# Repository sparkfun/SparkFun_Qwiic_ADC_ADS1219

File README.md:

[*SparkFun Qwiic 24 Bit ADC - 4 Channel (ADS1219) (SEN-27544)*](https://www.sparkfun.com/sparkfun-qwiic-24-bit-adc-4-channel-ads1219.html)

A lot of the time you just need to add more analog inputs to solve a problem. It happens. The SparkFun Qwiic 24-Bit ADC can provide four channels of I2C controlled ADC input to your Qwiic enabled project. These channels can be used as single-ended inputs, or in pairs for differential inputs, running at sample rates of up to 1kHz. What makes this ADC even more powerful is that it has a programmable x1 or x4 gain amplifier that lets you "zoom in" on a very small change in analog voltage (but will still effect your input range and resolution). Utilizing our handy Qwiic system, it is easy to connect it to the rest of your system. However, we have broken out 0.1"-spaced pads too in case you prefer to use a breadboard. The analog inputs and reference pins are all broken out on 0.1"-spaced pads too. This board does not have screw terminals - there was not enough room!

The ADS1219 can use its own internal 2.048V voltage reference for measurements, or you can provide your own reference via the REFP and REFN breakout pads. You can also provide your own VDDA (AVDD) by opening the jumper and connecting a voltage to the VDDA pad. This ADC board has eight address jumpers that let you choose one of sixteen unique addresses (0x40 to 0x4F). With these, you can connect up to sixteen of these on the same I2C bus and have 64 channels of ADC. The maximum resolution of the converter is 24-bits, corresponding to 244.14nV per count at a gain of x1. At a gain of x4, the resolution is 61.04nV per count. Note: the effective resolution is limited to 20-bits.

Repository Contents
-------------------

* **/docs** - GitHub pages documentation files
* **/Documentation** - TI datasheet 
* **/Hardware** - KiCad design files (_pcb, _sch), Schematic (PDF)
* **/Production** - Production panel files (_pcb, gerbers)

Documentation
--------------
* [**Arduino Library**](https://github.com/sparkfun/SparkFun_ADS1219_Arduino_Library) - Arduino library for the ADS1219.
* [**Hookup Guide**](https://docs.sparkfun.com/SparkFun_Qwiic_ADC_ADS1219/)

Product Versions
-----------------

* [SPX-23455](https://www.sparkfun.com/sparkx-qwiic-24-bit-adc-4-channel-ads1219.html) - Original SparkX release.
* [SEN-27544](https://www.sparkfun.com/sparkfun-qwiic-24-bit-adc-4-channel-ads1219.html) - Initial SparkFun release.

License Information
-------------------

This product is _**open source**_! 

Please review the LICENSE.md file for license information. 

If you have any questions or concerns on licensing, please contact technical support on our [SparkFun forums](https://forum.sparkfun.com/viewforum.php?f=152).

Distributed as-is; no warranty is given.

- Your friends at SparkFun.

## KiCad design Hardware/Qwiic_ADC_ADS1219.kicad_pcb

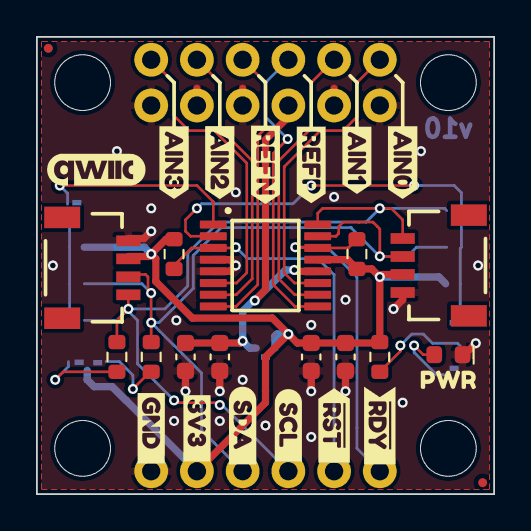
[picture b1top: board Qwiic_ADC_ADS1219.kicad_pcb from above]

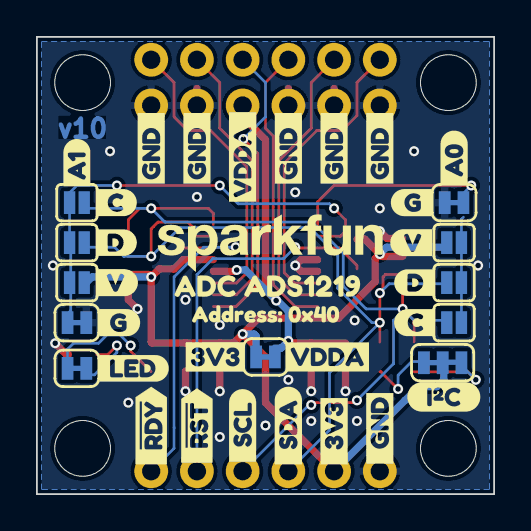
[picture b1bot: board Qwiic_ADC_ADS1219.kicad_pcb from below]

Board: 4 copper layers, 25.4 x 25.4 mm, 75 parts (39 on the bottom side), 19 nets.

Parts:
C1, C3: 2.2uF; C_0603_1608Metric
C2, C4: 0.1uF; C_0603_1608Metric
D1: Red; LED_0603_1608Metric_Red
FID1, FID3: Fiducial_0.5mm; Fiducial_0.5mm_Mask1mm
J1, J2: Qwiic_RA; JST_SMD_1.0mm-4_Black
J3, J4: Conn_01x06; 1x06
J5: Conn_01x02; 1x02
J6: I2C; 1x04
JP1, JP2: Jumper_2_NC_Trace
JP3: Jumper_3_NC-2_Trace
JP4, JP8: G; Jumper_2_NC_Trace
JP5, JP9: V; Jumper_2_NO
JP6, JP10: D; Jumper_2_NO
JP7, JP11: C; Jumper_2_NO
R1: 1k; R_0603_1608Metric
R2, R3: 2.2k; R_0603_1608Metric
R4, R5: 10k; R_0603_1608Metric
ST1, ST2, ST3, ST4: Standoff
U1: ADS1219IPW; TSSOP-16
kibuzzard-64C3B30F: G***; kibuzzard-64C3B30F
kibuzzard-64C3BD7A: G***; kibuzzard-64C3BD7A
kibuzzard-64C36D1A: G***; kibuzzard-64C36D1A
kibuzzard-64C36D2D: G***; kibuzzard-64C36D2D
kibuzzard-64C36D5B: G***; kibuzzard-64C36D5B
kibuzzard-64C36D6C: G***; kibuzzard-64C36D6C
kibuzzard-64C36D47: G***; kibuzzard-64C36D47
kibuzzard-64C36D91: G***; kibuzzard-64C36D91
kibuzzard-64C37A88: G***; kibuzzard-64C37A88
kibuzzard-64C37CC9: G***; kibuzzard-64C37CC9
kibuzzard-64C38090: G***; kibuzzard-64C38090
kibuzzard-67BCC03F: G***; kibuzzard-67BCC03F
kibuzzard-67BCE7E0: G***; kibuzzard-67BCE7E0
kibuzzard-67BCE9A5: G***; kibuzzard-67BCE9A5
kibuzzard-67BCE9C9: G***; kibuzzard-67BCE9C9
kibuzzard-67BCE9CD: G***; kibuzzard-67BCE9CD
kibuzzard-67BCE9E1: G***; kibuzzard-67BCE9E1
kibuzzard-67BCE80E: G***; kibuzzard-67BCE80E
kibuzzard-67BCE89D: G***; kibuzzard-67BCE89D
kibuzzard-67BCE805: G***; kibuzzard-67BCE805
kibuzzard-67BCE809: G***; kibuzzard-67BCE809
kibuzzard-67BCE889: G***; kibuzzard-67BCE889
kibuzzard-67BCE896: G***; kibuzzard-67BCE896
kibuzzard-67BCE899: G***; kibuzzard-67BCE899
kibuzzard-67BCEA1E: G***; kibuzzard-67BCEA1E
kibuzzard-67BCEA3A: G***; kibuzzard-67BCEA3A
kibuzzard-67BCEA31: G***; kibuzzard-67BCEA31
kibuzzard-67BCEA48: G***; kibuzzard-67BCEA48
kibuzzard-67BCEA55: G***; kibuzzard-67BCEA55
kibuzzard-67BCEA65: G***; kibuzzard-67BCEA65
kibuzzard-67BCEA70: G***; kibuzzard-67BCEA70
kibuzzard-67BCEAAB: G***; kibuzzard-67BCEAAB
kibuzzard-67BCEAC6, kibuzzard-67BCEAC6#2, kibuzzard-67BCEAC6#3, kibuzzard-67BCEAC6#4, kibuzzard-67BCEAC6#5: G***; kibuzzard-67BCEAC6
kibuzzard-67BCEAE1: G***; kibuzzard-67BCEAE1
kibuzzard-67BCEB1D: G***; kibuzzard-67BCEB1D
kibuzzard-67BCEB15: G***; kibuzzard-67BCEB15
kibuzzard-67BCEB32: G***; kibuzzard-67BCEB32

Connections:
3.3V: C1.1, C2.1, J1.2, J2.2, J6.2, JP1.1 (A), JP3.2 (B), JP5.2 (B), JP9.2 (B), R1.2, R4.2, R5.1, U1.13 (DVDD)
A0: JP4.1 (A), JP5.1 (A), JP6.1 (A), JP7.1 (A), U1.1 (A0)
A1: JP8.1 (A), JP9.1 (A), JP10.1 (A), JP11.1 (A), U1.2 (A1)
AIN0: J3.6, U1.11 (AIN0)
AIN1: J3.5, U1.10 (AIN1)
AIN2: J3.2, U1.7 (AIN2)
AIN3: J3.1, U1.6 (AIN3)
GND: C1.2, C2.2, C3.2, C4.2, D1.1 (K), J1.1, J2.1, J4.1, J4.2, J4.3, J4.5, J4.6, J6.1, JP4.2 (B), JP8.2 (B), U1.4 (DGND), U1.5 (AGND)
unnamed: D1.2 (A), JP2.1 (A)
unnamed: JP2.2 (B), R1.1
unnamed: JP3.1 (A), R3.1
unnamed: JP3.3 (C), R2.2
REFN: J3.3, U1.8 (REFN)
REFP: J3.4, U1.9 (REFP)
SCL: J1.4, J2.4, J6.4, JP7.2 (B), JP11.2 (B), R2.1, U1.16 (SCL)
SDA: J1.3, J2.3, J6.3, JP6.2 (B), JP10.2 (B), R3.2, U1.15 (SDA)
VDDA: C3.1, C4.1, J4.4, JP1.2 (B), U1.12 (AVDD)
~DRDY: J5.2, R4.1, U1.14 (~DRDY)
~RESET: J5.1, R5.2, U1.3 (~RESET)

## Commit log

2024-11-20 Transition to reds
    - Change PCB color to Red
    - Add "V10" stamp to B.Cu
    - Change SparkX Logo to SparkFun
    - No outstanding bugs in SPX repo, no circuit changes made
    - Generate new panel
2025-02-24 Update silk. Change address jumper names.
2025-10-07 Changes board setup to two layers and adds measures
2025-11-20 Main docs update
    This commit includes updated docs content, GH pages build files and other review updates.
2025-11-20 Update GH build file
    Updating to v3
2025-11-20 Removing extra readme
    Fixing copy/paste error w/extra readme file.
2026-02-24 Adding single page files
    Adding missing single page files and updating GH pages build file.
2026-02-24 Update mkdocs.yml
    Fixing typo
2026-02-24 Deployed 9b03edc with MkDocs version: 1.6.1
2026-06-05 Deployed de0f428 with MkDocs version: 1.6.1
